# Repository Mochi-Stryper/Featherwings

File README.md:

# Featherwings
 Unlicensed and Unverified Adafruit Peripherals

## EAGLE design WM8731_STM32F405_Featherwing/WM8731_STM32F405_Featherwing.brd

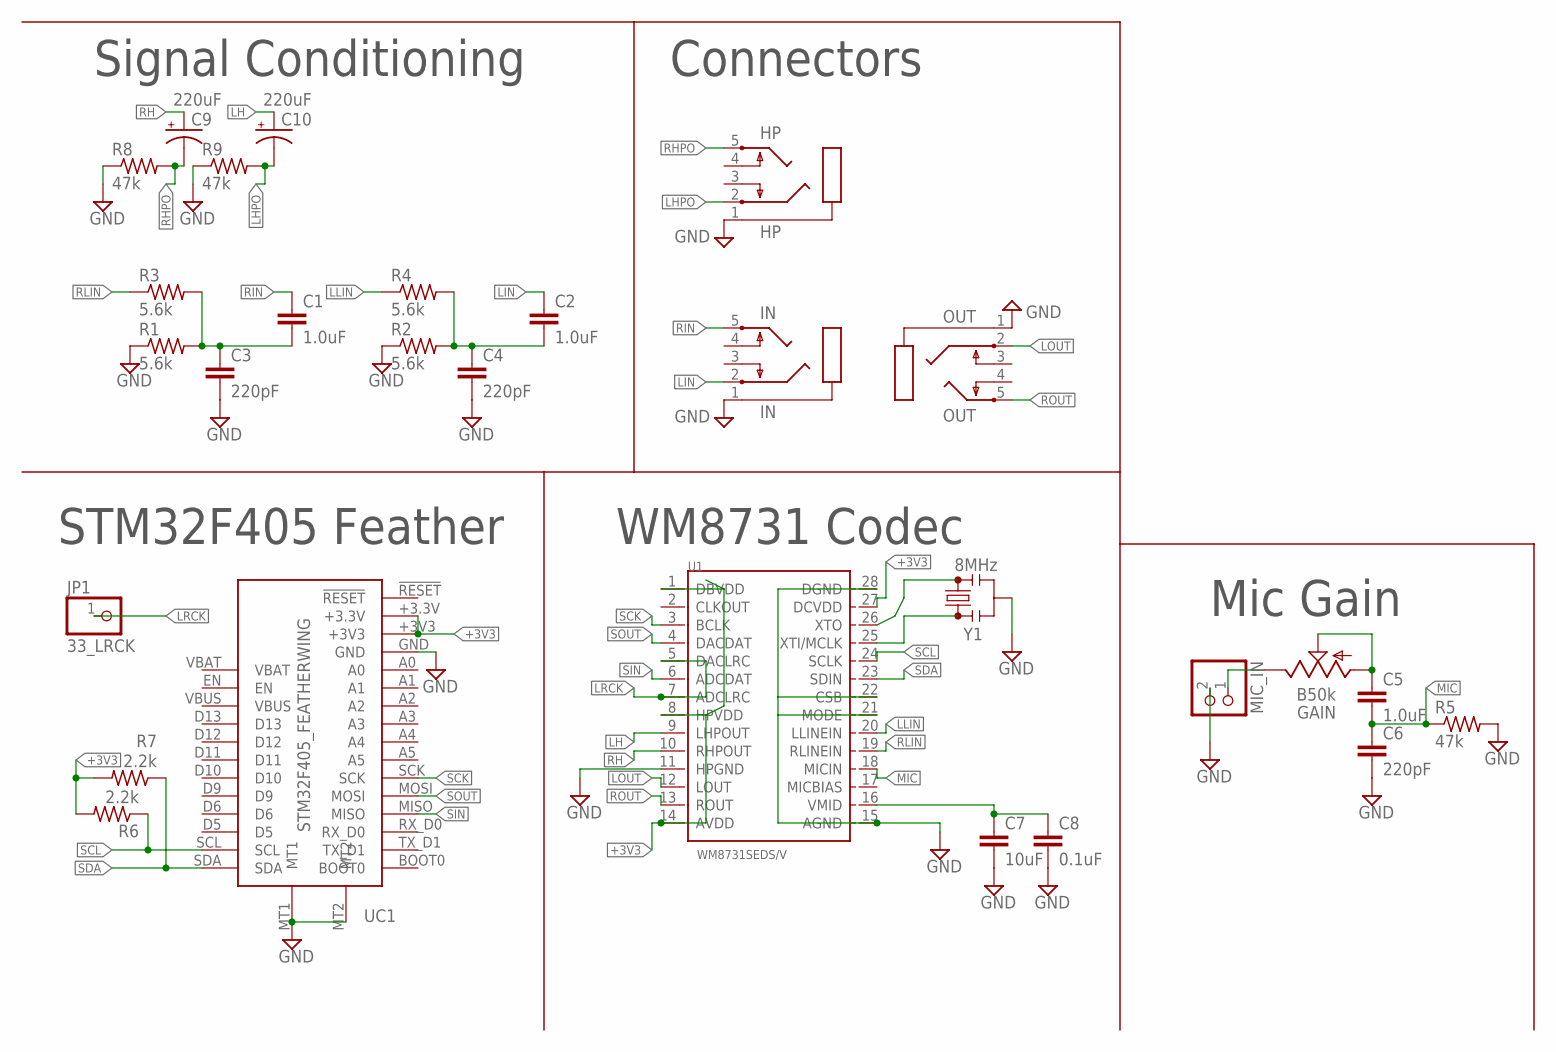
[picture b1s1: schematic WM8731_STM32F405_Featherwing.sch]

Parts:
C1, C2, C5: 1.0uF; 0402
C3, C4, C6: 220pF; 0402
C7: 10uF; 0603
C8: 0.1uF; 0402
C9, C10: 220uF; PANASONIC_D
GAIN: B50k; 9MM_SNAP-IN_POT
HP: HP; STX3100
IN: IN; STX3100
JP1: 33_LRCK; 1X01
MIC_IN: PINHD-1X2; 1X02
OUT: OUT; STX3100
R1, R2, R3, R4: 5.6k; R0402
R5, R8, R9: 47k; R0402
R6, R7: 2.2k; R0402
U1: WM8731SEDS/V; SSOP28-0.65-10.2X5.2MM
UC1: STM32F405_FEATHERWING
Y1: 8MHz; RESONATOR-SMD-3.2X1.3

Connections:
+3V3: R6.2, R7.2, U1.1 (DBVDD), U1.8 (HPVDD), U1.14 (AVDD), U1.27 (DCVDD), UC1.+3.3V, UC1.+3V3
GND: C3.2, C4.2, C6.2, C7.2, C8.2, HP.1, IN.1, MIC_IN.2, OUT.1, R1.1, R2.1, R5.2, R8.1, R9.1, U1.11 (HPGND), U1.15 (AGND), U1.21 (MODE), U1.22 (CSB), U1.28 (DGND), UC1.GND, UC1.MT1, UC1.MT2, Y1.2
LH: C10.+, U1.9 (LHPOUT)
LHPO: C10.-, HP.2, R9.2
LIN: C2.1, IN.2
LLIN: R4.1, U1.20 (LLINEIN)
LOUT: OUT.2, U1.12 (LOUT)
LRCK: JP1.1, U1.5 (DACLRC), U1.7 (ADCLRC)
MIC: C5.2, C6.1, R5.1, U1.18 (MICIN)
unnamed: U1.25 (XTI/MCLK), Y1.1
unnamed: U1.26 (XTO), Y1.3
unnamed: C2.2, C4.1, R2.2, R4.2
unnamed: C1.2, C3.1, R1.2, R3.2
unnamed: C5.1, GAIN.1 (A), GAIN.2 (S)
unnamed: C7.1, C8.1, U1.16 (VMID)
unnamed: GAIN.3 (E), MIC_IN.1
RH: C9.+, U1.10 (RHPOUT)
RHPO: C9.-, HP.5, R8.2
RIN: C1.1, IN.5
RLIN: R3.1, U1.19 (RLINEIN)
ROUT: OUT.5, U1.13 (ROUT)
SCK: U1.3 (BCLK), UC1.SCK
SCL: R6.1, U1.24 (SCLK), UC1.SCL
SDA: R7.1, U1.23 (SDIN), UC1.SDA
SIN: U1.6 (ADCDAT), UC1.MISO
SOUT: U1.4 (DACDAT), UC1.MOSI

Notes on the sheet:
Mic Gain
Connectors
STM32F405 Feather
WM8731 Codec
Signal Conditioning

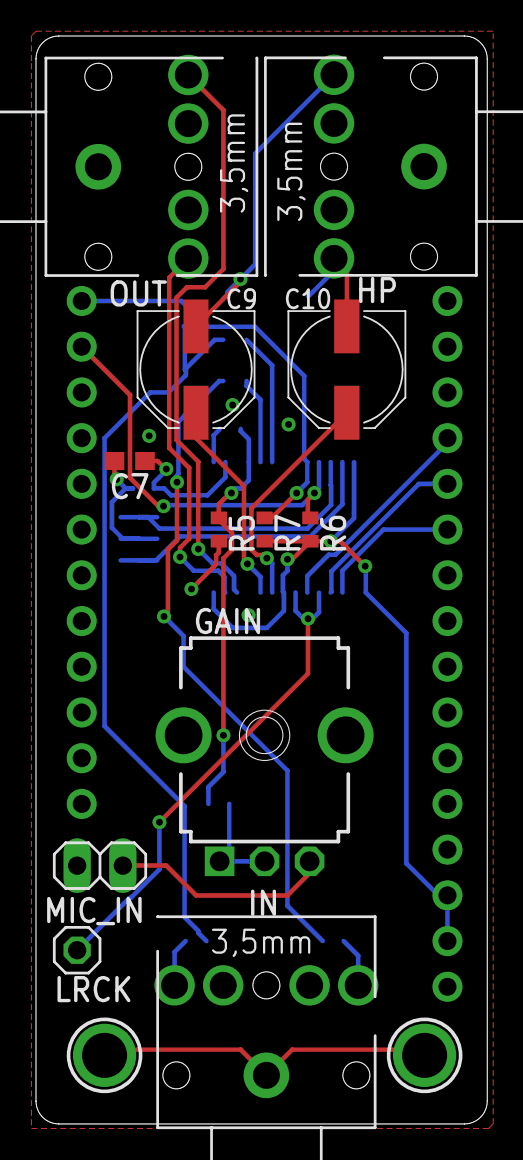
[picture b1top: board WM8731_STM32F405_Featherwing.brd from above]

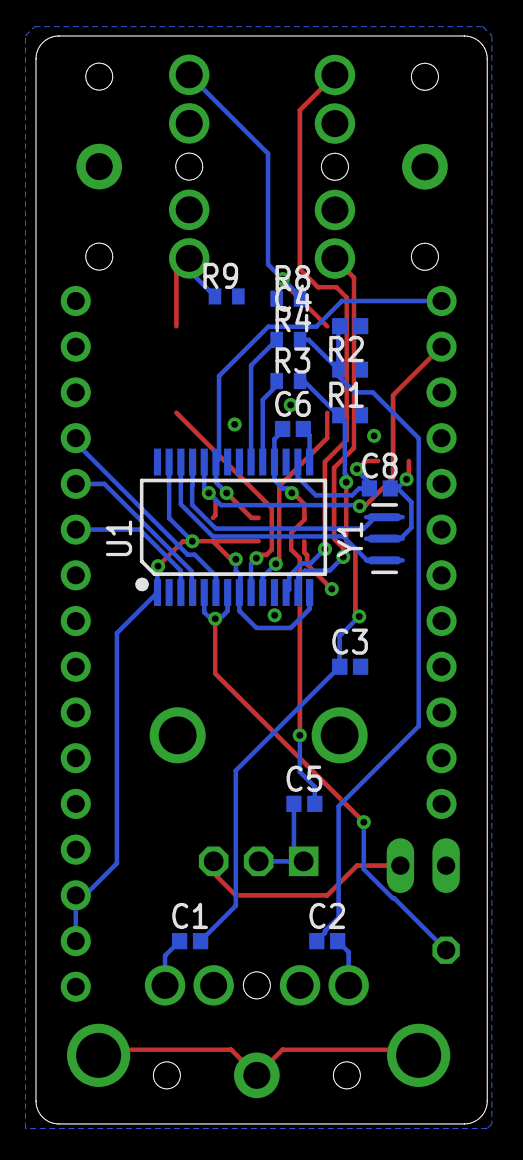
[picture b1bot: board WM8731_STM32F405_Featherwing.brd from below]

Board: 2 copper layers, 25.1 x 60.4 mm, 28 parts (15 on the bottom side), 26 nets.

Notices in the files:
parts and their libraries:
SparkFun-Capacitors: Licensing: Creative Commons ShareAlike 4.0 International - https://creativecommons.org/licenses/by-sa/4.0
